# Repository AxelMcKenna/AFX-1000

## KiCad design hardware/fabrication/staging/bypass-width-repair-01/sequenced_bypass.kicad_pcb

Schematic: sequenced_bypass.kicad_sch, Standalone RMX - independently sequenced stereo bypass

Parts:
C1: 150pF C0G 5%; C_0805_2012Metric
C2, C3, C4, C5, C6: 100nF X7R; C_0805_2012Metric
C7: 1uF 16V X7R; C_0805_2012Metric
C8: 22uF 16V X7R; C_1206_3216Metric
C9: 1uF 16V X7R 10%; C_0805_2012Metric
C10, C11, C12: 100nF 16V X7R; C_0805_2012Metric
D1, D2, D3: SMF9.0A; D_SOD-123F
J1, J7, J8: Conn_01x03; PinHeader_1x03_P2.54mm_Vertical
J2, J9: Conn_01x06; PinHeader_1x06_P2.54mm_Vertical
J3: Conn_01x05; PinHeader_1x05_P2.54mm_Vertical
J4: Conn_01x04; PinHeader_1x04_P2.54mm_Vertical
J5, J6: Conn_01x02; PinHeader_1x02_P2.54mm_Vertical
K1, K2: G6K-2F-Y DC5; Relay_DPDT_Omron_G6K-2F-Y
Q1, Q2, Q3: AO3400A; SOT-23
R1, R6: 10k 1%; R_0805_2012Metric
R2, R17, R18: 100k 1%; R_0805_2012Metric
R3, R4, R5, R7, R15: 47k 1%; R_0805_2012Metric
R8, R10, R12: 4.7k 1%; R_0805_2012Metric
R9, R11, R13: 270k 1%; R_0805_2012Metric
R14: 383k 0.1% 25ppm; R_0805_2012Metric
R16: 147k 1%; R_0805_2012Metric
U1: TPS3431SDRBR; TI_DRB0008A_TPS3431
U2, U6: SN74HCS08DR; SOIC-14_3.9x8.7mm_P1.27mm
U3: SN74LVC1G74DCTR; TI_DCT0008A_SN74LVC1G74
U4: TPS3808G33DBVR; SOT-23-6
U5: TPS3808G50DBVR; SOT-23-6
U7: LTC6994HS6-1#TRMPBF; TSOT-23-6
U8: SN74HCS86DR; SOIC-14_3.9x8.7mm_P1.27mm

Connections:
/3V3: C2.1, C3.1, C4.1, C5.1, C6.1, C7.1, C10.1, C11.1, C12.1, J1.3, J3.1, R1.1, R6.1, R16.1, R18.1, U1.1 (VDD), U1.3 (EN), U1.5 (SET1), U2.14 (VCC), U3.2 (D), U3.7 (PRE_N), U3.8 (VCC), U4.3 (MR_N), U4.5 (SENSE), U4.6 (VDD), U5.3 (MR_N), U5.6 (VDD), U6.14 (VCC), U7.5 (V+), U8.5 (2B), U8.14 (VCC)
/5V: C8.1, J1.1, J4.1, J4.3, J5.1, K1.1 (COIL+), K2.1 (COIL+), U5.5 (SENSE)
/AGND: C1.2, C2.2, C3.2, C4.2, C5.2, C6.2, C7.2, C8.2, C9.2, C10.2, C11.2, C12.2, D1.2, D2.2, D3.2, J1.2, J2.1, J3.4, J6.1, J7.2, J8.2, J9.2, J9.5, Q1.2 (S), Q2.2 (S), Q3.2 (S), R2.2, R3.2, R4.2, R5.2, R7.2, R9.2, R11.2, R13.2, R14.2, R17.2, U1.4 (AGND), U1.9 (EP), U2.7 (AGND), U3.4 (AGND), U4.2 (AGND), U5.2 (AGND), U6.7 (GND), U7.2 (GND), U8.7 (GND), U8.9 (3A), U8.10 (3B), U8.12 (4A), U8.13 (4B)
/ANALOG_OK: J3.3, R5.1, U2.2 (1B)
/ARMED: J2.5, U2.9 (3A), U3.3 (Q)
/BYPASS_GATE: Q1.1 (G), R8.2, R9.1
/BYPASS_LOW: D1.1, J4.2, K1.8 (COIL-), Q1.3 (D)
/BYPASS_SENSE: J2.6, J3.5, R6.2
/CLEAR_N: U3.6 (CLR_N), U6.5 (2B), U6.8 (3Y)
/COIL_ENABLE: U2.8 (3Y), U6.4 (2A)
/CWD: C1.1, U1.2 (CWD)
/FINAL_ENABLE: R8.1, U6.6 (2Y)
/GAIN_DELAY: C9.1, R15.2, U8.2 (1B)
/GAIN_EDGE: U8.3 (1Y), U8.4 (2A)
/GAIN_GATE: Q2.1 (G), R10.2, R11.1
/GAIN_LOW: D2.1, J5.2, Q2.3 (D)
/GAIN_REQ: J2.4, R7.1, R10.1, R15.1, U8.1 (1A)
/GAIN_STABLE: U6.13 (4B), U8.6 (2Y)
/HEARTBEAT: J2.2, R2.1, U1.6 (WDI)
/INPUT_ENABLE: R12.1, U2.3 (1Y), U2.4 (2A), U6.12 (4A)
/INPUT_GATE: Q3.1 (G), R12.2, R13.1
/INPUT_LOW: D3.1, J4.4, K2.8 (COIL-), Q3.3 (D)
/INPUT_READY: J6.2, U6.3 (1Y), U6.9 (3A)
/IN_L: J7.1, K1.2 (L_NC), K2.4 (L_NO)
/IN_R: J7.3, K1.7 (R_NC), K2.5 (R_NO)
/LOCAL_OK: R1.2, U1.7 (WDO_N), U1.8 (ENOUT), U2.1 (1A), U4.1 (RESET_N), U5.1 (RESET_N)
/MCU_PERMIT: J2.3, R3.1, U2.12 (4A), U2.13 (4B)
/OUT_L: J8.1, K1.3 (L_COM)
/OUT_R: J8.3, K1.6 (R_COM)
/PERMIT_CLEAN: U2.10 (3B), U2.11 (4Y), U3.1 (CLK)
/PROCESS_HEALTH: U2.6 (2Y), U6.10 (3B)
/PROCESS_OK: J3.2, R4.1, U2.5 (2B)
/PROC_IN_L: J9.1, K2.3 (L_COM)
/PROC_IN_R: J9.3, K2.6 (R_COM)
/PROC_OUT_L: J9.4, K1.4 (L_NO)
/PROC_OUT_R: J9.6, K1.5 (R_NO)
/STARTUP_CT: R18.2, U4.4 (CT)
/TIMER_DIV: R16.2, R17.1, U7.4 (DIV)
/TIMER_ENABLE: U6.1 (1A), U6.11 (4Y), U7.1 (IN)
/TIMER_INPUT_OK: U6.2 (1B), U7.6 (OUT)
/TIMER_SET: R14.1, U7.3 (SET)

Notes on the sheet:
E11: independent input precharge and edge-armed wet output. All blocks show physical package pin numbers.
Replaces E02+E03 for the external F02 profile; do not assemble all three projects together. No PCB or physical validation.
K2 closes on LOCAL_OK & ANALOG_OK; manual bypass clears K1 only. Gain edges restart U7, holding K1 dry for ~2s.
INPUT_READY -> MCP0x22 GPA3, no pull-up, receiving 270k pull-down. Firmware adds 1.25s quiet + 350ms stable rearm.
Common AGND reference; keep coil returns away from audio paths. Rail monitors, complete integrated PCB, harnesses and bench tests remain open.

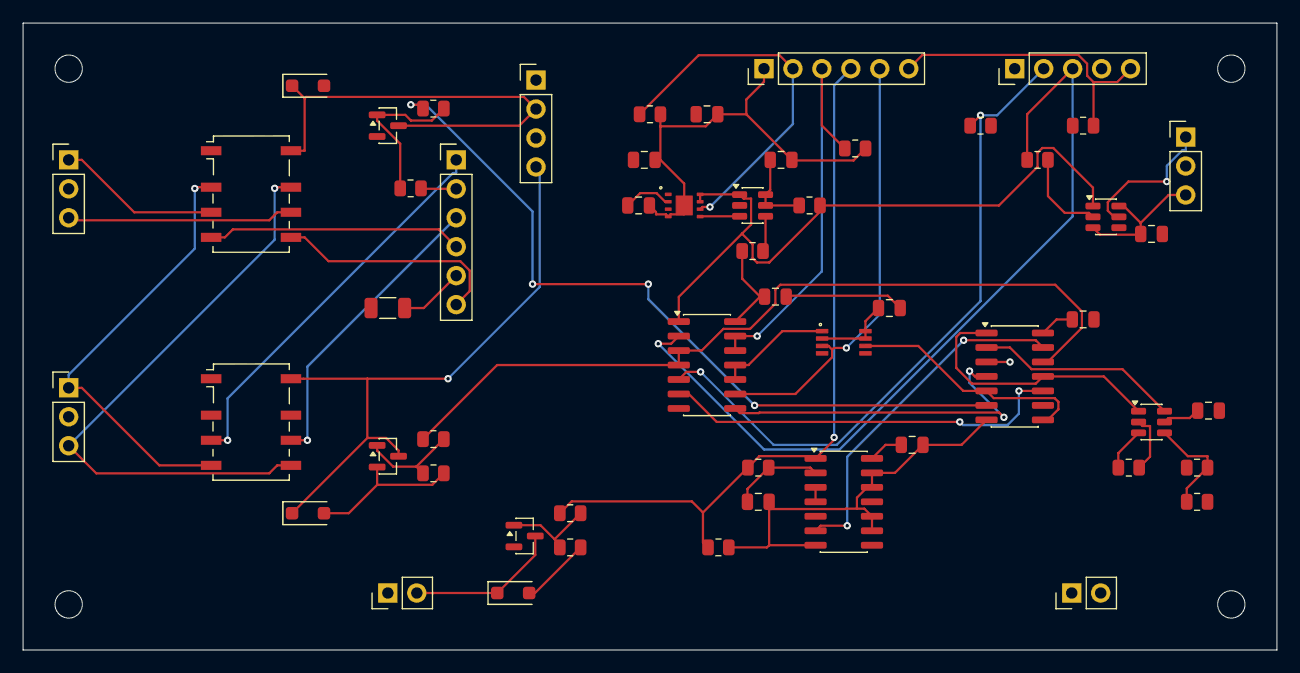
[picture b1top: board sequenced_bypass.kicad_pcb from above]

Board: 4 copper layers, 110.0 x 55.0 mm, 59 parts (0 on the bottom side), 41 nets.

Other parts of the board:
H1, H2, H3, H4: M2_CLEARANCE; M2_Clearance

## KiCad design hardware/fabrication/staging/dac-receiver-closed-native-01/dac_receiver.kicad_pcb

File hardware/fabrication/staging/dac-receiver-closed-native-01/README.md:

# E08 receiver layout integration candidate

This is the first routed physical candidate for the existing 60-part E08
receiver circuit. It closes the receiver-only layout gap. It does **not**
close the final codec/ADC/receiver audio-board integration or release a PCB
for fabrication.

Open [the portable KiCad project](dac_receiver.kicad_pro),
[the routing preview](plots/routing-review.png),
[native top view](plots/top/top.svg),
[native bottom view](plots/bottom/bottom.svg),
[native review](review.json), or [independent handoff](layout-handoff.json).

## Checked construction

- 84 × 64 × 1.6 mm planning envelope; 60 electrical parts and four M2
  clearance holes. This envelope has not been placed in the housing.
- Four copper layers: F.Cu/B.Cu signal and supply tracks; In1.Cu/In2.Cu
  AGND zones. Stackup materials and finished copper are not a fabricator contract.
- 338 segments and 41 conventional through vias. All native DRC, open
  connection, schematic-parity and ERC counts are zero in pinned Linux
  KiCad 10.0.7, with every native check enabled.
- All original E08 component values, footprints and numbered pin nets match
  both the original exported circuit and its independent electrical contract.
  Routing preserves the checked placement, outline and authored zones.
- 34 amplifier feedback/summing connections have continuous F.Cu chains at
  least 0.2 mm wide. The largest sum of whole segments in these chains is
  13.884 mm; the I/V chains reach at most 7.656 mm. This measures construction,
  including segment overhangs, rather than parasitics or stability margins.
- The independent native-polygon screen checks all 41 via drills against all
  SMD lands. Its smallest drill-edge/copper separation is 0.200 mm before
  manufacturing tolerances. Mask, stencil, drill registration and assembly
  acceptance remain separate requirements.

## Integration requirements

J1 retains the **prototype circuit boundary**, with the same pin order as E09.
It is not an approved raw-DAC harness or final product connector. The codec
and its I/V amplifiers must be co-located on the final audio PCB; that work
must reconsider the current J1 routes and recheck the shared ground, ADC
force/sense stars, digital coupling and power distribution. The receiver
region can inform this placement; its present outline and mounting holes
are not the final physical partition.

ESS raw DAC current, DC/common-mode and output-impedance conventions remain
unresolved. The circuit preserves the existing reference-derived I/V gain
without claiming the modeled 2 V RMS normalization is the chip's full scale.
Obtain the manufacturer data and resolve the gain/calibration range before
releasing the integrated design. See
[the existing circuit limits](../../../electronics/dac_receiver/README.md).

Exact passive/connector selections, film-capacitor maximum dimensions and
mounting, ±12 V supply/return behavior, thermal design and enclosure fit still
need review. The 1-second analog/codec settling requirement still applies.
First-article bring-up must keep processed audio muted until qualified;
measured noise, distortion, stability, clipping and fault behavior remain
post-fabrication qualification work.

## Reproduction and evidence

The construction chain is `dac-receiver-stock-01` →
`dac-receiver-placement-02` → `dac-receiver-placement-native-02` →
`dac-receiver-routing-01` → `dac-receiver-routed-native-01` →
`dac-receiver-ground-stitches-01` → this native-refilled project.
`dac-receiver-closed-inputs-01/capture.json` is the native copper capture used
for independent geometry checks. Earlier unsuccessful placement evidence
is retained as earlier revisions and does not support this candidate.

The placement recipe is
[`dac_receiver_layout.py`](../../dac_receiver_layout.py); router interchange
and ground stitching use the existing bounded tools. Native operations use
the pinned, offline Linux container. No Mac KiCad/OpenSCAD process was launched.
No source circuit was regenerated or altered, and no order or upload was sent.

Replay the circuit, native-evidence, placement and feedback audit without CAD:

```sh
.venv/bin/python -m hardware.fabrication.audit_dac_receiver --check
```

These are engineering checks for a development candidate. The complete unit
and this receiver candidate remain unreleased.

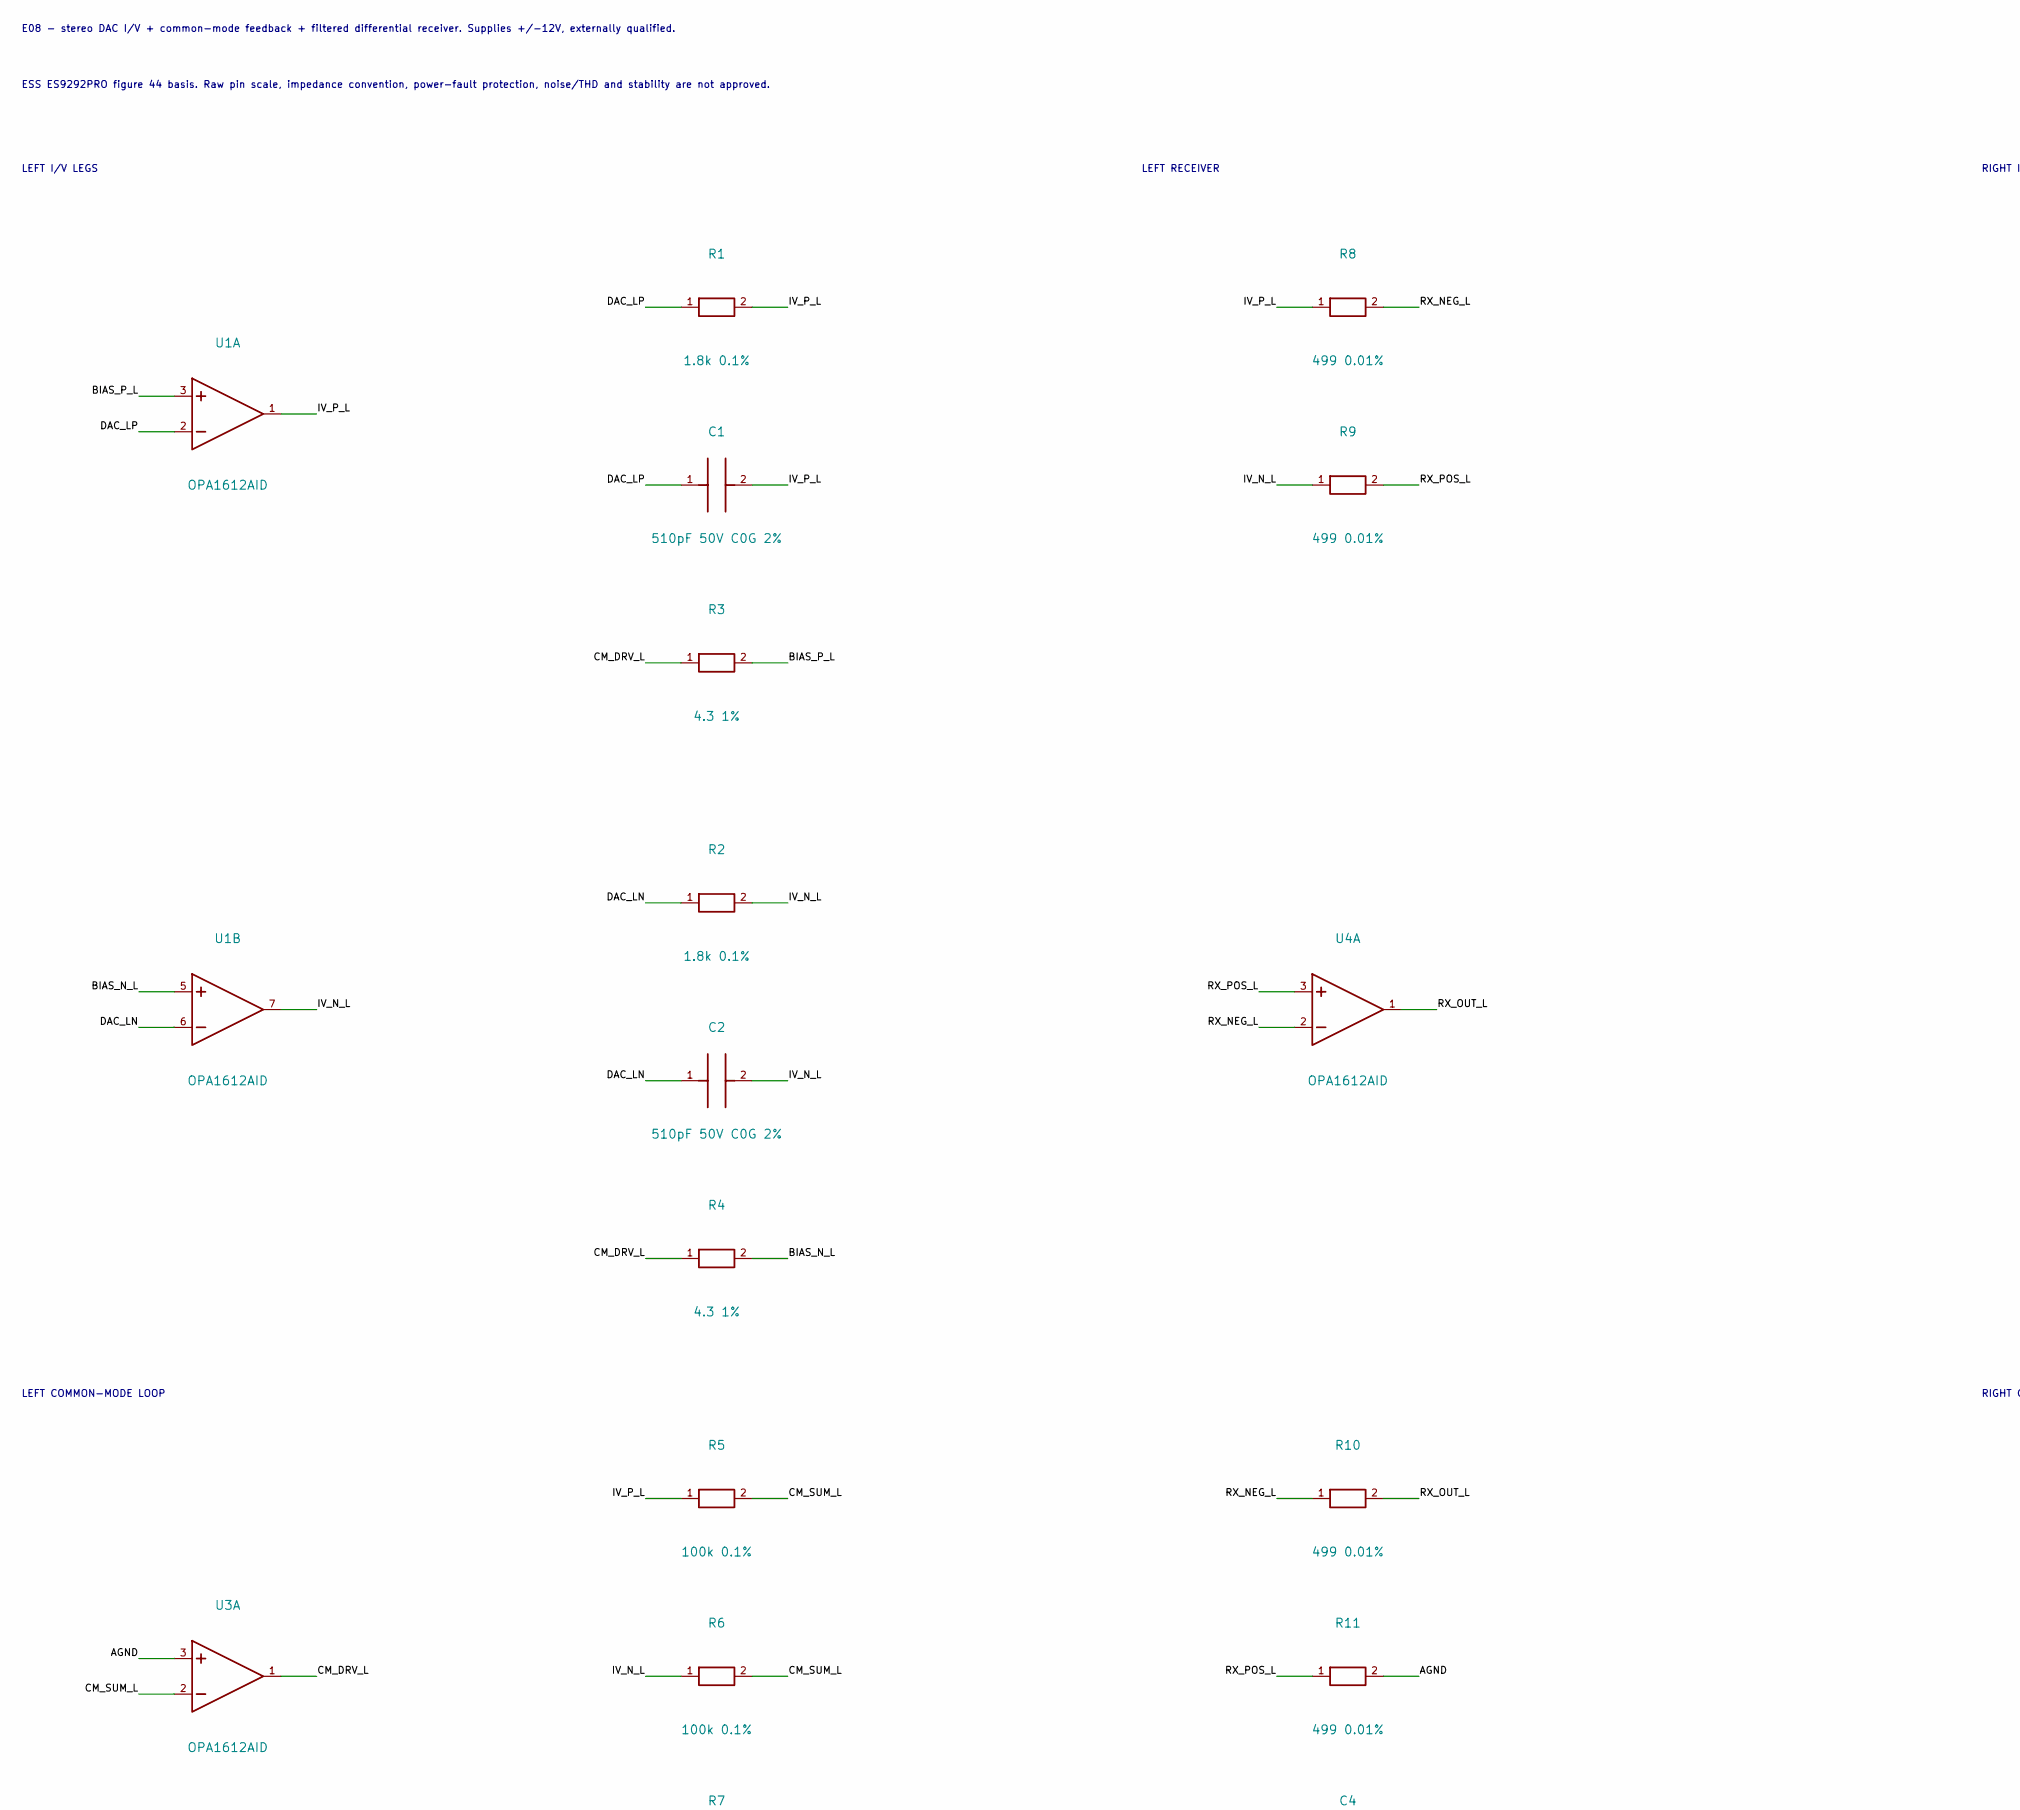
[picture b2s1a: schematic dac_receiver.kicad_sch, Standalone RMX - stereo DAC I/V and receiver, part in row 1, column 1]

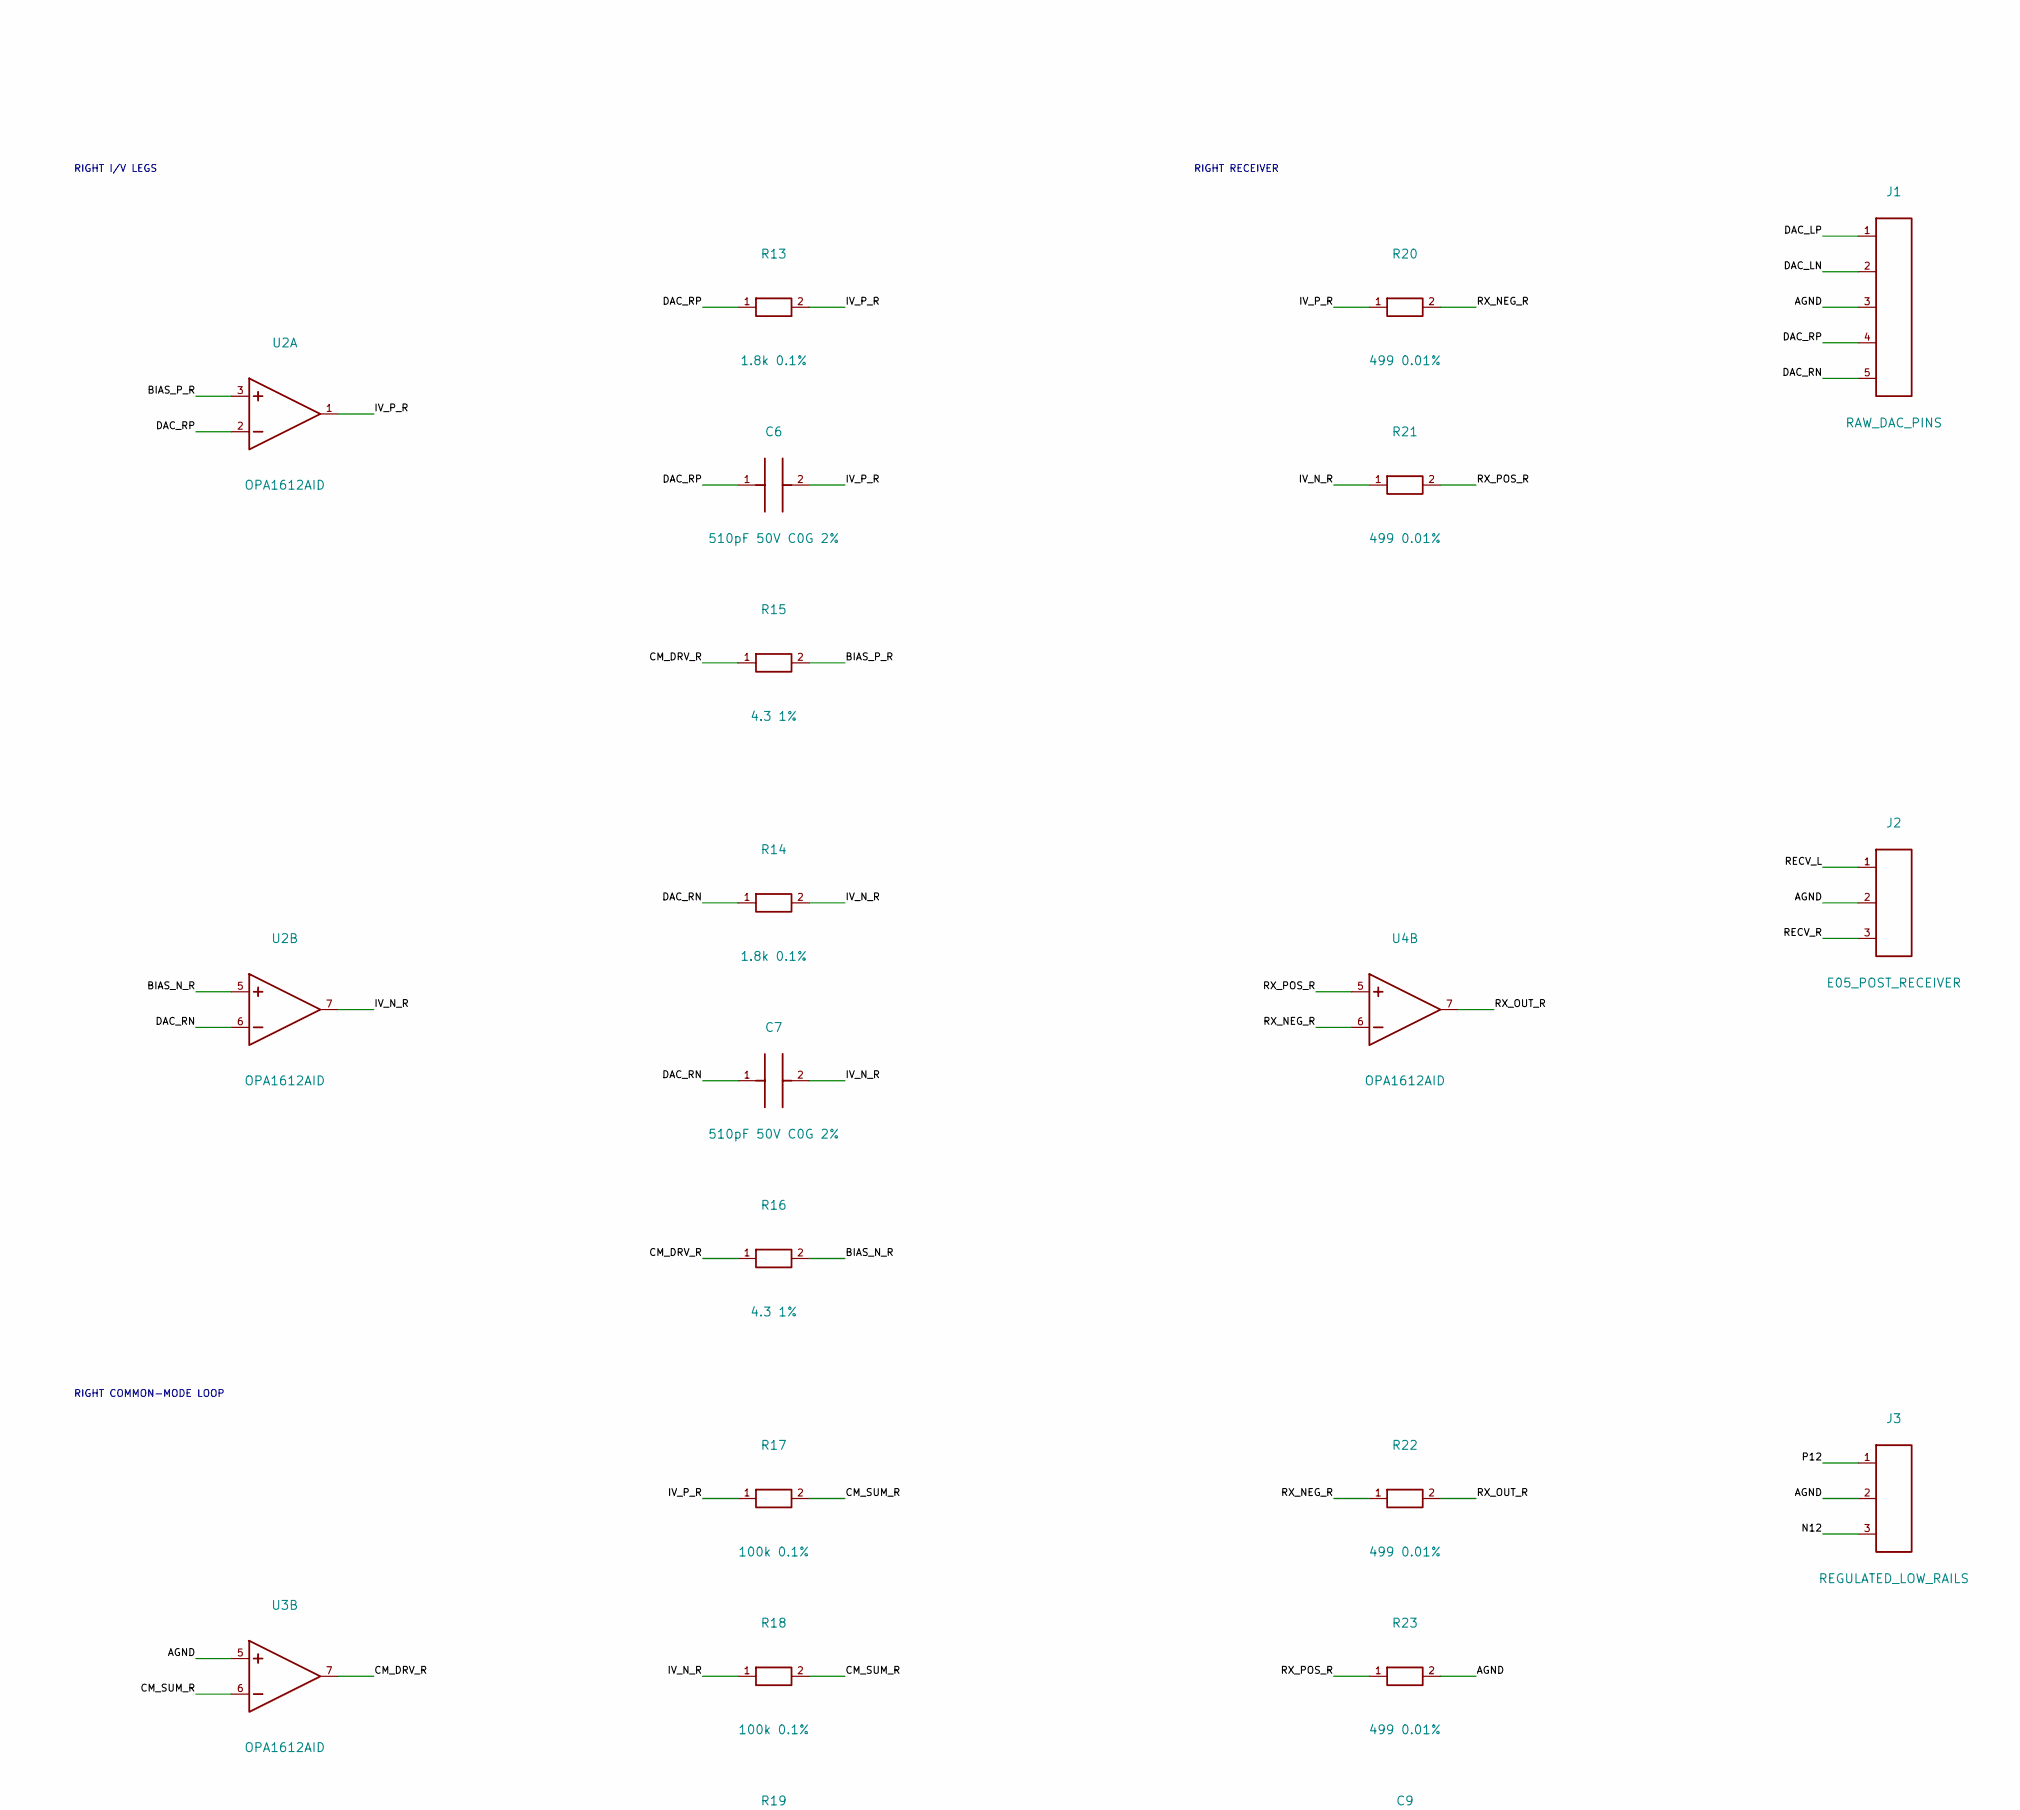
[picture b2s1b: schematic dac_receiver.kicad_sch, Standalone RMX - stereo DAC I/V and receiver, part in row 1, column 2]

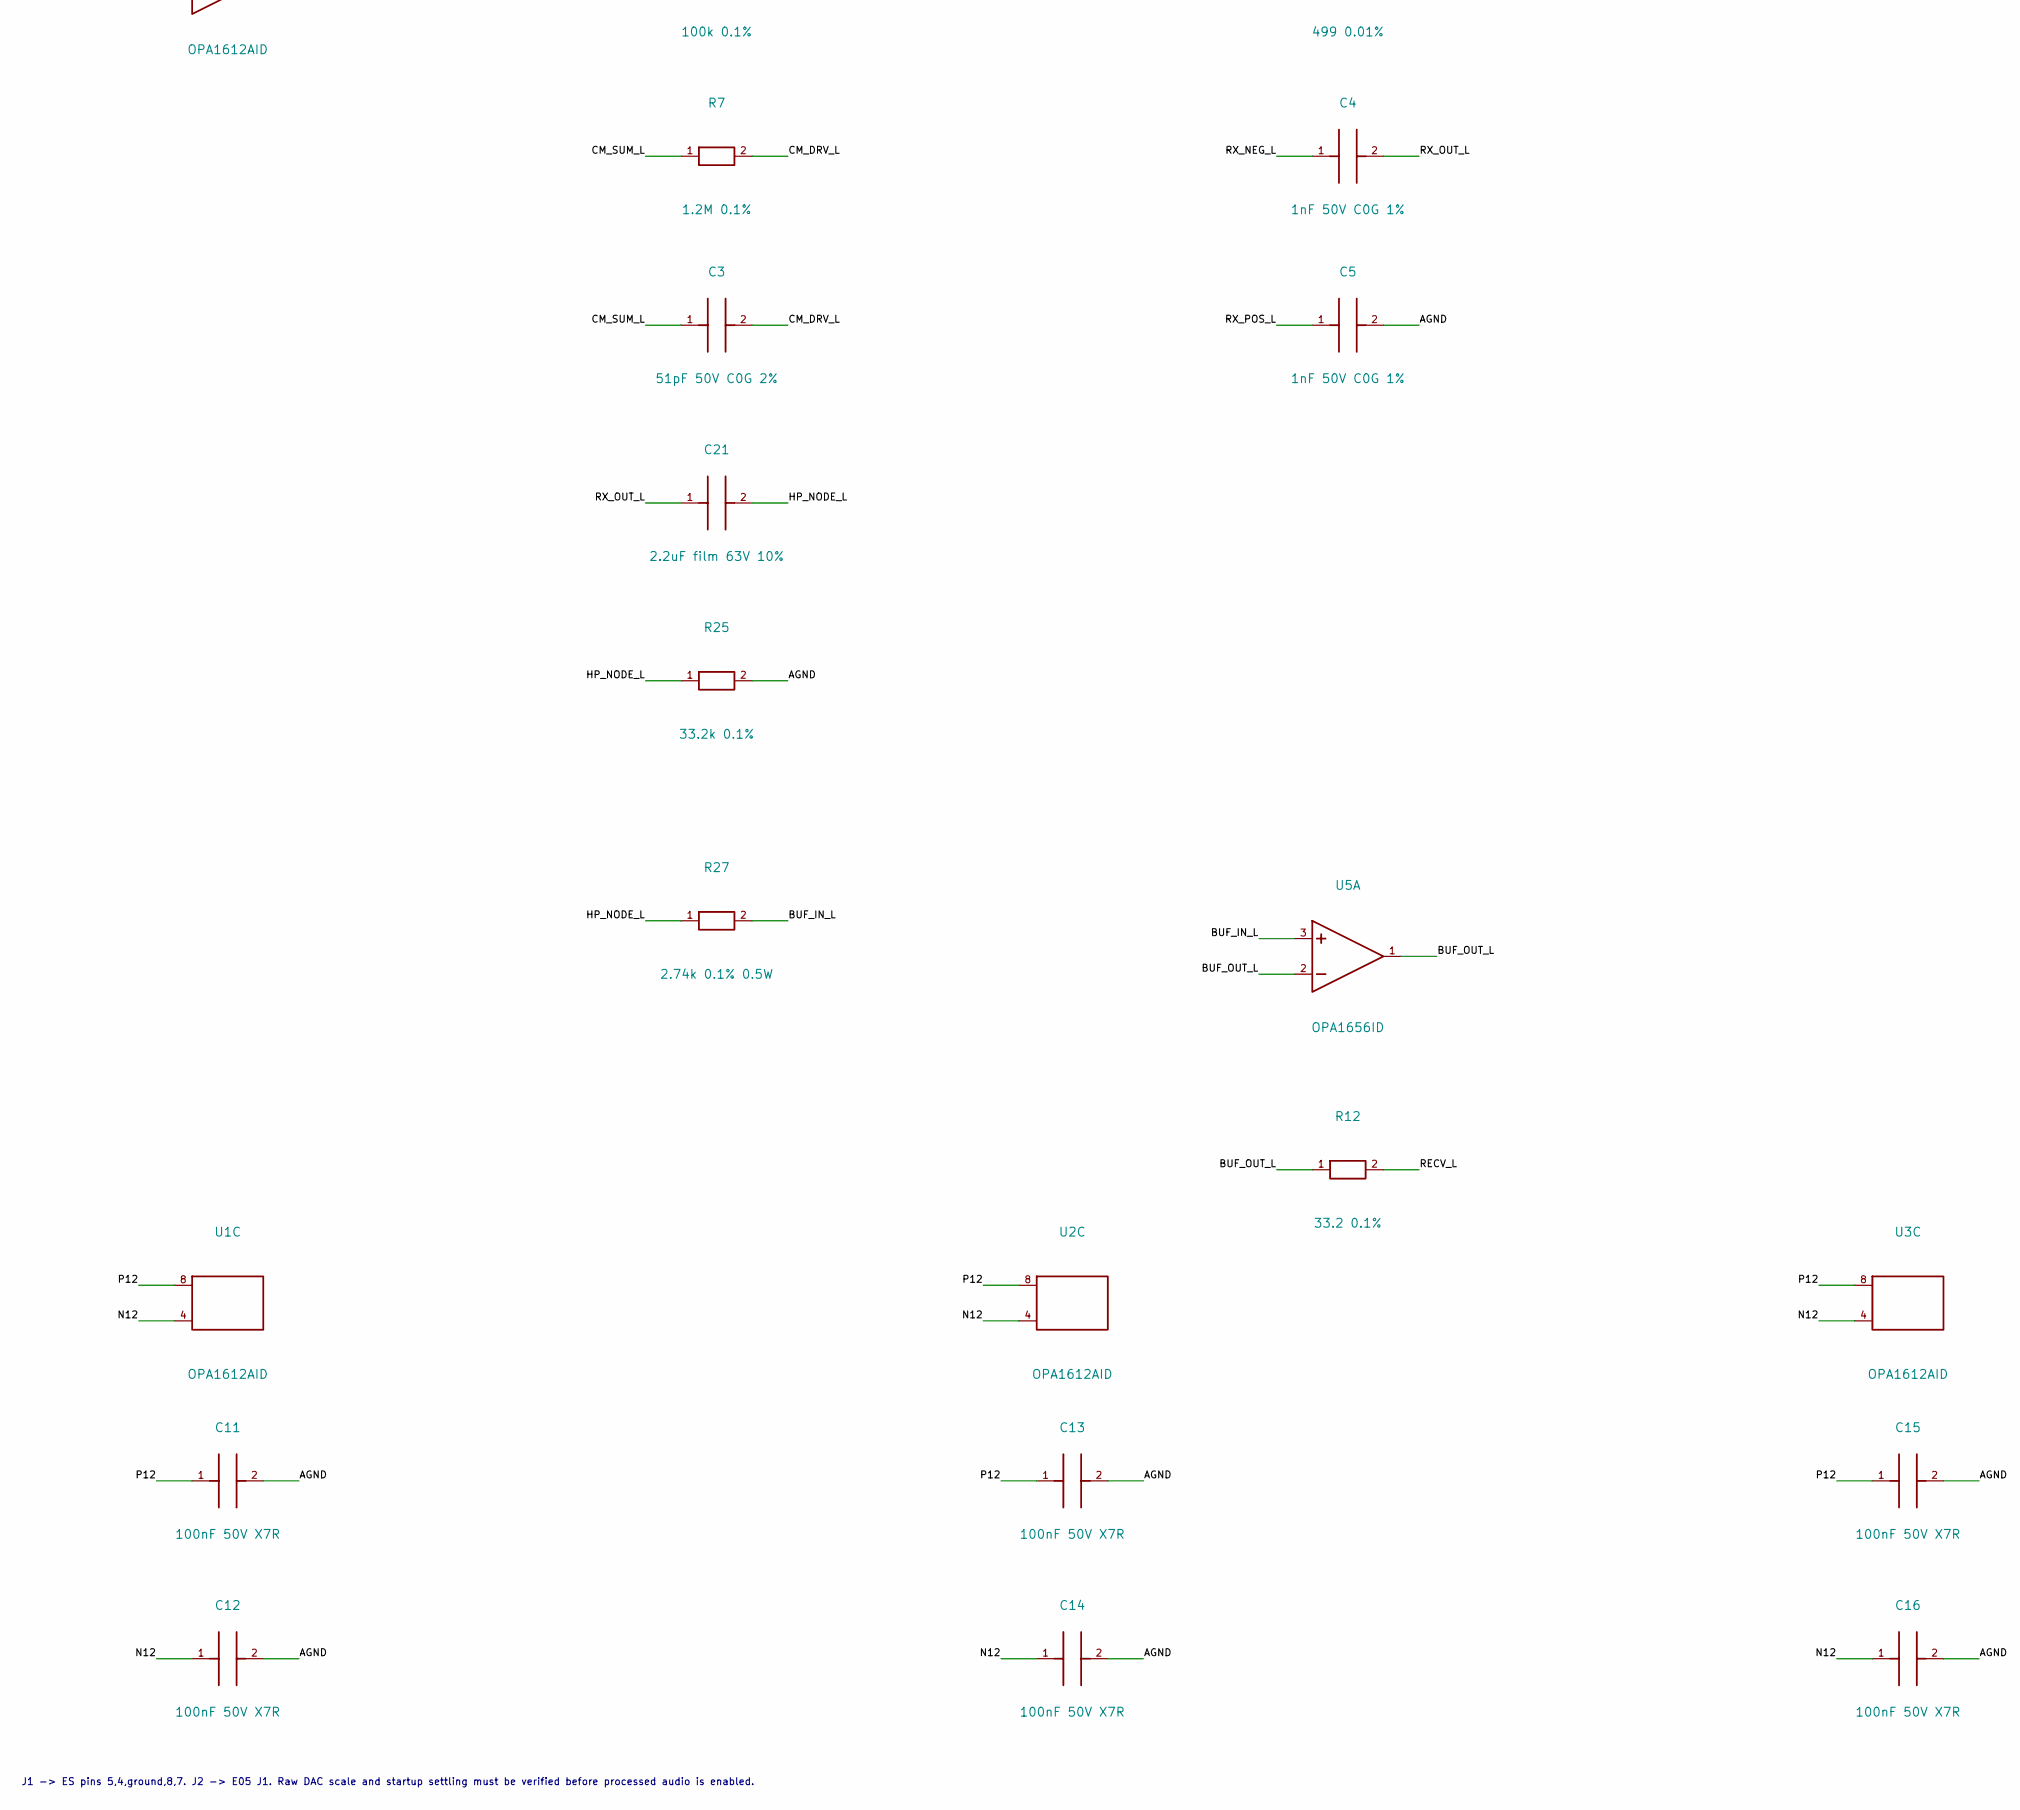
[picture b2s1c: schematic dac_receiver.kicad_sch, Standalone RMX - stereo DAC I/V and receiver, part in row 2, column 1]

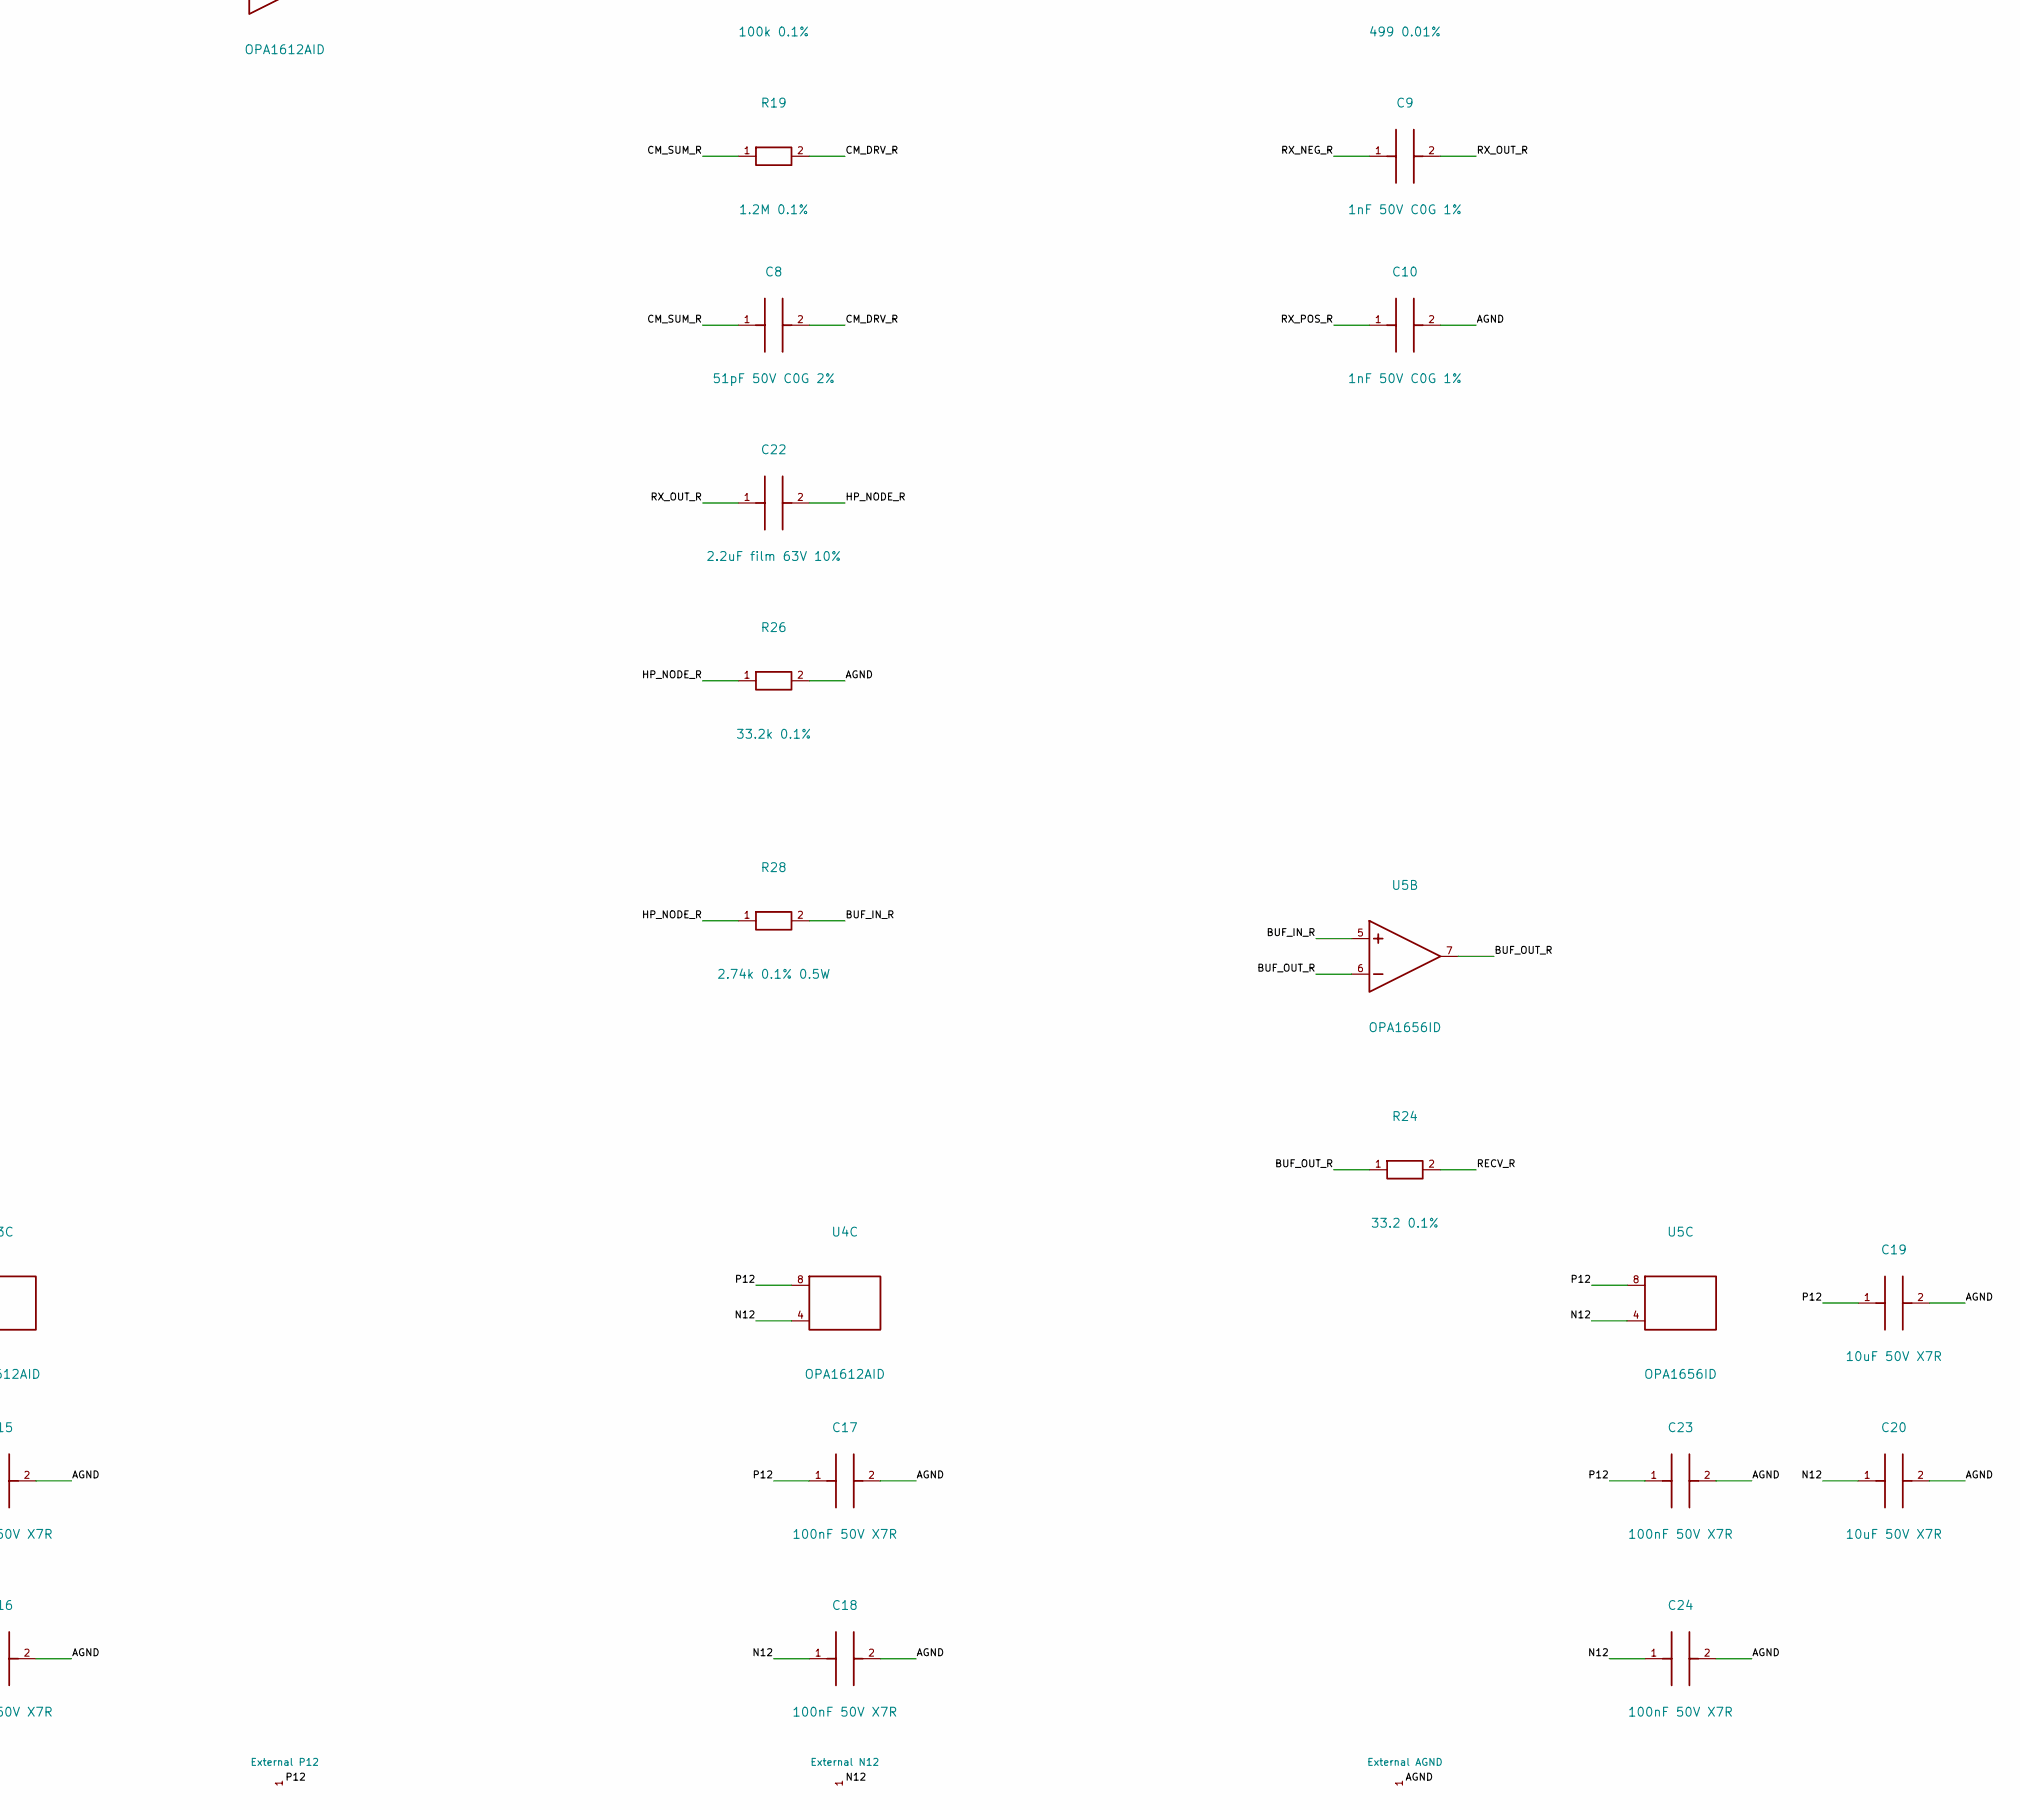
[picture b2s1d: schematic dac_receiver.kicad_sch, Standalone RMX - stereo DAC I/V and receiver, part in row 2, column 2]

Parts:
C1, C2, C6, C7: 510pF 50V C0G 2%; C_0805_2012Metric
C3, C8: 51pF 50V C0G 2%; C_0805_2012Metric
C4, C5, C9, C10: 1nF 50V C0G 1%; C_0805_2012Metric
C11, C12, C13, C14, C15, C16, C17, C18, C23, C24: 100nF 50V X7R; C_0805_2012Metric
C19, C20: 10uF 50V X7R; C_1210_3225Metric
C21, C22: 2.2uF film 63V 10%; C_Rect_L7.2mm_W7.2mm_P5.00mm_FKS2_FKP2_MKS2_MKP2; MPN MKS2C042201K00KSSD
J1: RAW_DAC_PINS; PinHeader_1x05_P2.54mm_Vertical
J2: E05_POST_RECEIVER; PinHeader_1x03_P2.54mm_Vertical
J3: REGULATED_LOW_RAILS; PinHeader_1x03_P2.54mm_Vertical
R1, R2, R13, R14: 1.8k 0.1%; R_0805_2012Metric
R3, R4, R15, R16: 4.3 1%; R_0805_2012Metric
R5, R6, R17, R18: 100k 0.1%; R_0805_2012Metric
R7, R19: 1.2M 0.1%; R_0805_2012Metric
R8, R9, R10, R11, R20, R21, R22, R23: 499 0.01%; R_0805_2012Metric
R12, R24: 33.2 0.1%; R_0805_2012Metric
R25, R26: 33.2k 0.1%; R_0805_2012Metric
R27, R28: 2.74k 0.1% 0.5W; R_2010_5025Metric
U1, U2, U3, U4: OPA1612AID; SOIC-8_3.9x4.9mm_P1.27mm; MPN OPA1612AID
U5: OPA1656ID; SOIC-8_3.9x4.9mm_P1.27mm; MPN OPA1656ID

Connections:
/AGND: C5.2, C10.2, C11.2, C12.2, C13.2, C14.2, C15.2, C16.2, C17.2, C18.2, C19.2, C20.2, C23.2, C24.2, J1.3, J2.2, J3.2, R11.2, R23.2, R25.2, R26.2, U3.3 (+), U3.5 (+)
/BIAS_N_L: R4.2, U1.5 (+)
/BIAS_N_R: R16.2, U2.5 (+)
/BIAS_P_L: R3.2, U1.3 (+)
/BIAS_P_R: R15.2, U2.3 (+)
/BUF_IN_L: R27.2, U5.3 (+)
/BUF_IN_R: R28.2, U5.5 (+)
/BUF_OUT_L: R12.1, U5.1 (OUT), U5.2 (-)
/BUF_OUT_R: R24.1, U5.6 (-), U5.7 (OUT)
/CM_DRV_L: C3.2, R3.1, R4.1, R7.2, U3.1 (OUT)
/CM_DRV_R: C8.2, R15.1, R16.1, R19.2, U3.7 (OUT)
/CM_SUM_L: C3.1, R5.2, R6.2, R7.1, U3.2 (-)
/CM_SUM_R: C8.1, R17.2, R18.2, R19.1, U3.6 (-)
/DAC_LN: C2.1, J1.2, R2.1, U1.6 (-)
/DAC_LP: C1.1, J1.1, R1.1, U1.2 (-)
/DAC_RN: C7.1, J1.5, R14.1, U2.6 (-)
/DAC_RP: C6.1, J1.4, R13.1, U2.2 (-)
/HP_NODE_L: C21.2, R25.1, R27.1
/HP_NODE_R: C22.2, R26.1, R28.1
/IV_N_L: C2.2, R2.2, R6.1, R9.1, U1.7 (OUT)
/IV_N_R: C7.2, R14.2, R18.1, R21.1, U2.7 (OUT)
/IV_P_L: C1.2, R1.2, R5.1, R8.1, U1.1 (OUT)
/IV_P_R: C6.2, R13.2, R17.1, R20.1, U2.1 (OUT)
/N12: C12.1, C14.1, C16.1, C18.1, C20.1, C24.1, J3.3, U1.4 (V-), U2.4 (V-), U3.4 (V-), U4.4 (V-), U5.4 (V-)
/P12: C11.1, C13.1, C15.1, C17.1, C19.1, C23.1, J3.1, U1.8 (V+), U2.8 (V+), U3.8 (V+), U4.8 (V+), U5.8 (V+)
/RECV_L: J2.1, R12.2
/RECV_R: J2.3, R24.2
/RX_NEG_L: C4.1, R8.2, R10.1, U4.2 (-)
/RX_NEG_R: C9.1, R20.2, R22.1, U4.6 (-)
/RX_OUT_L: C4.2, C21.1, R10.2, U4.1 (OUT)
/RX_OUT_R: C9.2, C22.1, R22.2, U4.7 (OUT)
/RX_POS_L: C5.1, R9.2, R11.1, U4.3 (+)
/RX_POS_R: C10.1, R21.2, R23.1, U4.5 (+)

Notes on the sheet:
E08 - stereo DAC I/V + common-mode feedback + filtered differential receiver. Supplies +/-12V, externally qualified.
ESS ES9292PRO figure 44 basis. Raw pin scale, impedance convention, power-fault protection, noise/THD and stability are not approved.
LEFT I/V LEGS
LEFT RECEIVER
RIGHT I/V LEGS
RIGHT RECEIVER
LEFT COMMON-MODE LOOP
RIGHT COMMON-MODE LOOP
J1 -> ES pins 5,4,ground,8,7. J2 -> E05 J1. Raw DAC scale and startup settling must be verified before processed audio is enabled.

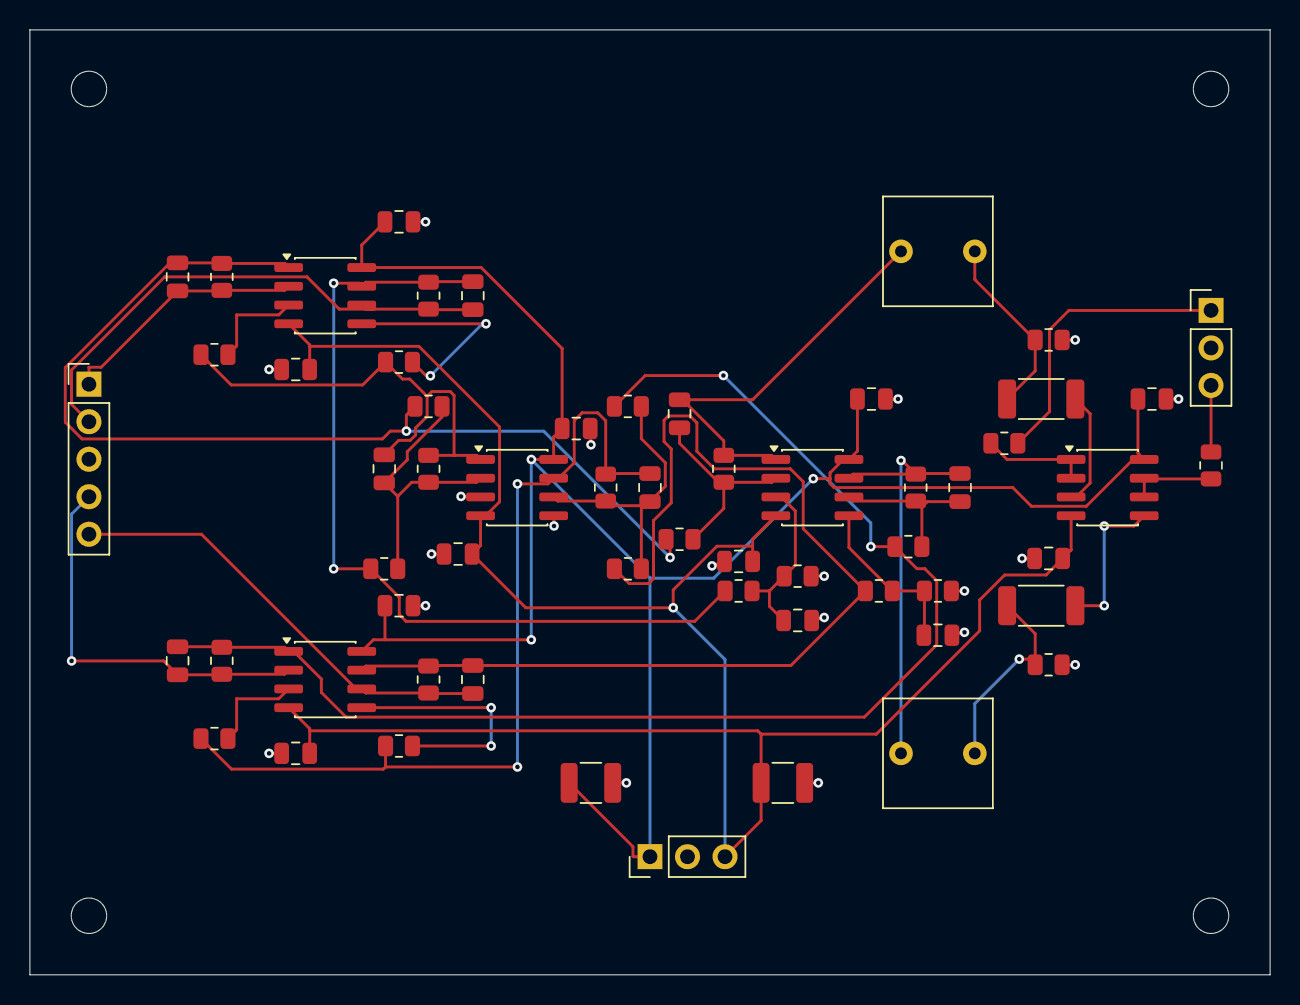
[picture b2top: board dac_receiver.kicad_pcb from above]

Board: 4 copper layers, 84.0 x 64.0 mm, 64 parts (0 on the bottom side), 33 nets.

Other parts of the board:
H1, H2, H3, H4: M2_CLEARANCE; M2_Clearance
